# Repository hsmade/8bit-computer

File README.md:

# My 8-bit computer

This repo describes my homebrew 8-bit computer. 
It is loosely based on the works of  [Ben eater's 6502 computer](https://eater.net/6502), and others.

A build log can be found [here](https://hsmade.github.io/8bit-computer)

## Components
### CPU card
This card contains the CPU and the RAM.

To be built.

* more info [here](CPU/README.md)
* the schematics can be found [here](CPU/kicad/)

### ROM card
This card holds the rom, and exposes a pin header for programming.
I currently do the programming with an Arduino Mega (because I need a lot of IO ports).
The software for programming the eeprom can be found [here](ROM/programmer/README.md)

* more info [here](ROM/README.md).
* the schematic can be found [here](ROM/kicad/).

### Bus display card
This card shows the current contents of the address and data bus, and if the CPU is reading or writing.
I used the trick to alternate between 2 displays, using a timer, from Ben Eater.
This doesn't use the whole flip-flop setup though, as I use just 2 displays per 8 bits (hex).

* more info [here](bus-display/README.md)
* the schematic can be found [here](bus-display/kicad/).

### IO card
This card will interface with the outside world.
The idea is to control a 1602A display, and a serial port.

To be designed and built.

## Requirements
The following software is required to run makefiles:
* cc65
* platformio

## Memory map
http://wilsonminesco.com/6502primer/addr_decoding.html

| start | end  | what     | A15 | A14 | A13 | A12 | A11 | A10 | A9 | A8 | A3 | A2 |
|-------|------|----------|-----|-----|-----|-----|-----|-----|----|----|----|----|
| 0000  | 3FFF | RAM      |   0 |   0 |   x |   x |   x |   x |  x |  x |  x |  x |
| 4100  |      | ACIA 3-1 |   0 |   1 |   0 |   0 |   0 |   0 |  0 |  1 |  0 |  0 |
| 4104  |      | ACIA 3-2 |   0 |   1 |   0 |   0 |   0 |   0 |  0 |  1 |  0 |  1 |
| 4108  |      | ACIA 3-3 |   0 |   1 |   0 |   0 |   0 |   0 |  0 |  1 |  1 |  0 |
| 410C  |      | ACIA 3-4 |   0 |   1 |   0 |   0 |   0 |   0 |  0 |  1 |  1 |  1 |
| 4200  |      | ACIA 2-1 |   0 |   1 |   0 |   0 |   0 |   0 |  1 |  0 |  0 |  0 |
| 4204  |      | ACIA 2-2 |   0 |   1 |   0 |   0 |   0 |   0 |  1 |  0 |  0 |  1 |
| 4208  |      | ACIA 2-3 |   0 |   1 |   0 |   0 |   0 |   0 |  1 |  0 |  1 |  0 |
| 420C  |      | ACIA 2-4 |   0 |   1 |   0 |   0 |   0 |   0 |  1 |  0 |  1 |  1 |
| 4400  | 4403 | ACIA 1   |   0 |   1 |   0 |   0 |   0 |   1 |  0 |  0 |  0 |  0 |
| 4800  | 480F | VIA 3    |   0 |   1 |   0 |   0 |   1 |   0 |  0 |  0 |  x |  x |
| 5000  | 500F | VIA 2    |   0 |   1 |   0 |   1 |   0 |   0 |  0 |  0 |  x |  x |
| 6000  | 600F | VIA 1    |   0 |   1 |   1 |   0 |   0 |   0 |  0 |  0 |  x |  x |
| 8000  | FFFF | ROM      |   1 |   x |   x |   x |   x |   x |  x |  x |  x |  x |

`A1` and `A0` select registers inside each ACIA. `A3` through `A0`
select registers inside each VIA. `A7` through `A4` are not decoded in
this memory map.

## Bus

| Use | Port | Port | Use   |
|-----|------|------|-------|
| VSS | 1    | 40   | VSS   |
| X   | 2    | 39   | Phi 0 |
| X   | 3    | 38   | X     |
| +5V | 4    | 37   | +5V   |
| A0  | 5    | 36   | X     |
| A1  | 6    | 35   | CSb   |
| A2  | 7    | 34   | RES   |
| A3  | 8    | 33   | NMI   |
| A4  | 9    | 32   | IRQ   |
| A5  | 10   | 31   | Phi 1 |
| A6  | 11   | 30   | Phi 2 |
| A7  | 12   | 29   | RWb   |
| A8  | 13   | 28   | D7    |
| A9  | 14   | 27   | D6    |
| A10 | 15   | 26   | D5    |
| A11 | 16   | 25   | D4    |
| A12 | 17   | 24   | D3    |
| A13 | 18   | 23   | D2    |
| A14 | 19   | 22   | D1    |
| A15 | 20   | 21   | D0    |

## Datasheets
* NAND [74HC00](https://www.mouser.com/catalog/specsheets/nxp_74hc_hct00.pdf)
* CPU [W65C02](https://nl.mouser.com/datasheet/2/436/w65c02s-2572.pdf)
* Power transistor PNP [BD952](https://nl.mouser.com/datasheet/2/54/bd646-1159083.pdf)
* RAM [39SF010A7CPHE](https://nl.mouser.com/datasheet/2/268/20005022C-1832260.pdf)
* 7 segment display [INND-TS40Y*CB](https://nl.mouser.com/datasheet/2/180/INND-TS40_Series_V1.0-1485199.pdf)
* ROM [SST39SF010A](https://nl.mouser.com/datasheet/2/268/20005022C-1832260.pdf)
* ACIA [W65C51](https://nl.mouser.com/datasheet/2/436/WDC_Datasheet%20Update_20141024-1211725.pdf)
* PIO [W65C22](https://nl.mouser.com/datasheet/2/436/w65c22-1197.pdf)

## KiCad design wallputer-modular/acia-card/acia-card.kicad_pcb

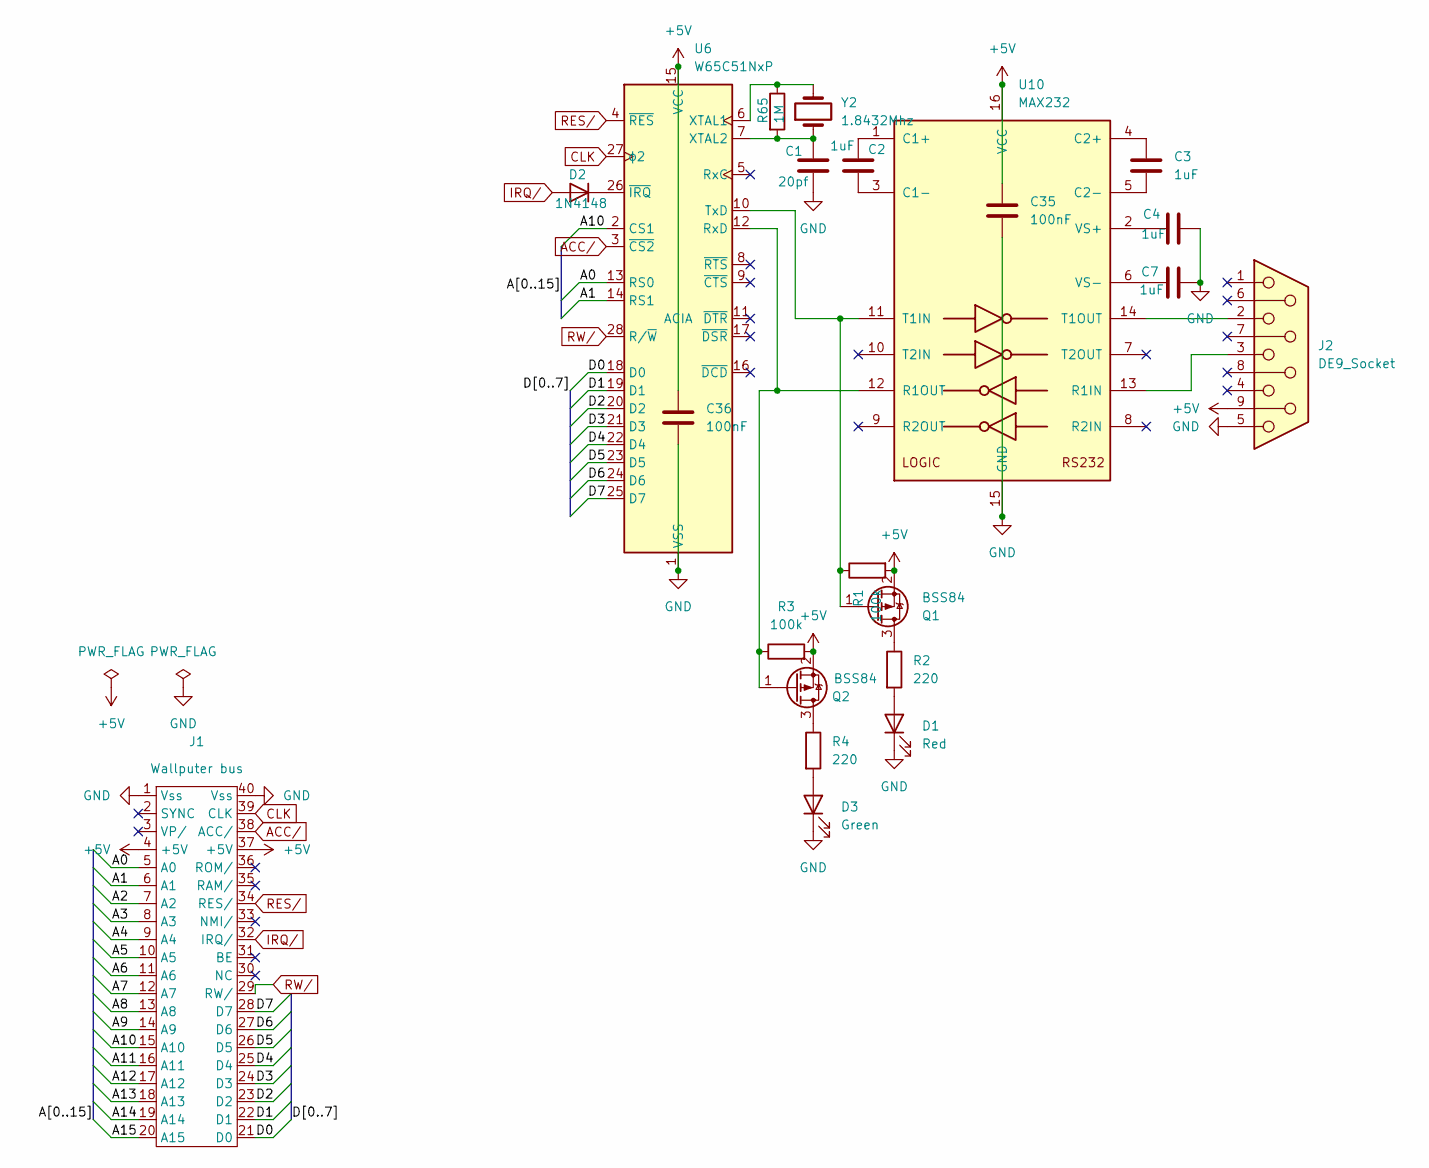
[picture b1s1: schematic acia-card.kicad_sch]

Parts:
C1: 20pf; C_Disc_D5.0mm_W2.5mm_P5.00mm
C2, C3, C4, C7: 1uF; C_Disc_D5.0mm_W2.5mm_P5.00mm
C35, C36: 100nF; C_Disc_D5.0mm_W2.5mm_P5.00mm
D1: Red; LED_D1.8mm_W3.3mm_H2.4mm
D2: 1N4148; D_DO-35_SOD27_P7.62mm_Horizontal
D3: Green; LED_D1.8mm_W3.3mm_H2.4mm
J1: Wallputer_Bus_Header
J2: DE9_Socket; DSUB-9_Pins_Horizontal_P2.77x2.84mm_EdgePinOffset4.94mm_Hou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
Q1, Q2: BSS84; SOT-23
R1, R3: 100k; R_Axial_DIN0204_L3.6mm_D1.6mm_P2.54mm_Vertical
R2, R4: 220; R_Axial_DIN0204_L3.6mm_D1.6mm_P2.54mm_Vertical
R65: 1M; R_Axial_DIN0204_L3.6mm_D1.6mm_P2.54mm_Vertical
U6: W65C51NxP; DIP-28_W15.24mm
U10: MAX232; DIP-16_W7.62mm_Socket
Y2: 1.8432Mhz; Crystal_HC18-U_Vertical

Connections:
+5V: C35.1, C36.1, J1.4 (+5V), J1.37 (+5V), J2.9, Q1.2 (S), Q2.2 (S), R1.2, R3.2, U6.15 (VCC), U10.16 (VCC)
/A0: J1.5 (A0), U6.13 (RS0)
/A1: J1.6 (A1), U6.14 (RS1)
/A2: J1.7 (A2)
/A3: J1.8 (A3)
/A4: J1.9 (A4)
/A5: J1.10 (A5)
/A6: J1.11 (A6)
/A7: J1.12 (A7)
/A8: J1.13 (A8)
/A9: J1.14 (A9)
/A10: J1.15 (A10), U6.2 (CS1)
/A11: J1.16 (A11)
/A12: J1.17 (A12)
/A13: J1.18 (A13)
/A14: J1.19 (A14)
/A15: J1.20 (A15)
/D0: J1.21 (D0), U6.18 (D0)
/D1: J1.22 (D1), U6.19 (D1)
/D2: J1.23 (D2), U6.20 (D2)
/D3: J1.24 (D3), U6.21 (D3)
/D4: J1.25 (D4), U6.22 (D4)
/D5: J1.26 (D5), U6.23 (D5)
/D6: J1.27 (D6), U6.24 (D6)
/D7: J1.28 (D7), U6.25 (D7)
ACC/: J1.38 (ACC/), U6.3 (~CS2)
CLK: J1.39 (CLK), U6.27 (ϕ2)
GND: C1.2, C4.2, C7.2, C35.2, C36.2, D1.1 (K), D3.1 (K), J1.1 (Vss), J1.40 (Vss), J2.5, U6.1 (VSS), U10.15 (GND)
IRQ/: D2.2 (A), J1.32 (IRQ/)
unnamed: D1.2 (A), R2.2
unnamed: D2.1 (K), U6.26 (~IRQ)
unnamed: D3.2 (A), R4.2
unnamed: Q1.3 (D), R2.1
unnamed: Q1.1 (G), R1.1, U6.10 (TxD), U10.11 (T1IN)
unnamed: Q2.3 (D), R4.1
unnamed: Q2.1 (G), R3.1, U6.12 (RxD), U10.12 (R1OUT)
unnamed: R65.1, U6.6 (XTAL1), Y2.2
unnamed: C1.1, R65.2, U6.7 (XTAL2), Y2.1
unnamed: C2.1, U10.1 (C1+)
unnamed: C2.2, U10.3 (C1-)
unnamed: C3.1, U10.4 (C2+)
unnamed: C3.2, U10.5 (C2-)
unnamed: J2.3, U10.13 (R1IN)
unnamed: J2.2, U10.14 (T1OUT)
unnamed: C4.1, U10.2 (VS+)
unnamed: C7.1, U10.6 (VS-)
RES/: J1.34 (RES/), U6.4 (~RES)
RW/: J1.29 (RW/), U6.28 (R/~W)

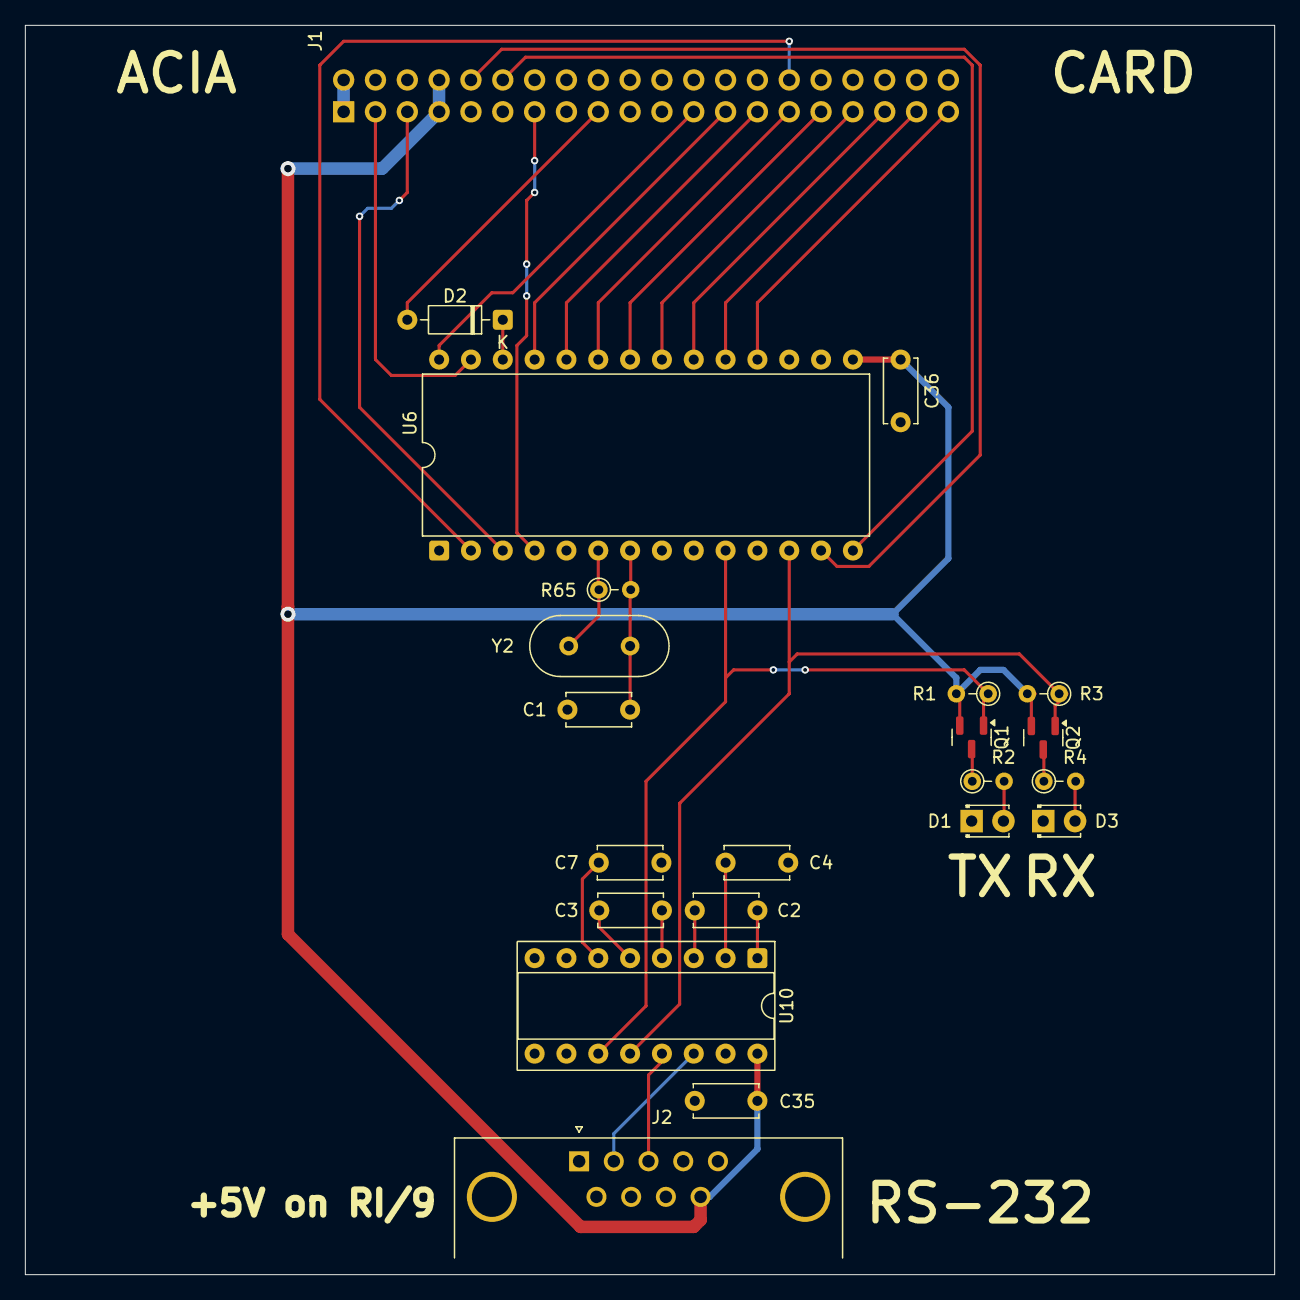
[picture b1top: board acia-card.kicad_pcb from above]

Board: 2 copper layers, 99.7 x 99.7 mm, 22 parts (0 on the bottom side), 35 nets.

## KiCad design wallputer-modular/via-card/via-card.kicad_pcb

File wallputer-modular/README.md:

# Modular Wall-Computer

## Setup
|  |  |  |  |
| -- | -- | -- | -- |
|  | [Clock Card](#clock-card) | [CPU Card](#cpu-card) | [Memory Card](#memory-card) |
| [Power Card](#power-card) | [Backplane Card](#backplane-card) | [Backplane Card](#backplane-card) | [Backplane Card](#backplane-card) |
|  | [Bus Display Card](#bus-display-card) | [ACIA Card](#acia-card) | [VIA Card](#via-card) |

## TODO

* finish up BOM using order
* check all footprints
* verify 555 circuits
* verify dual led circuit
* design rp2040 circuit
* verify clock switch circuit
* brightness via bars
* brightness RS-232 leds

## ACIA Card
Used for serial ports.

## Backplane Card

## Bus Display Card

## Clock Card
Generates the clock signal to steer the CPU and other components.

## CPU Card

## Memory Card

## Power Card
Power input and bus signal LEDs.

## VIA Card
I/O ports (LCD display, other stuff..)

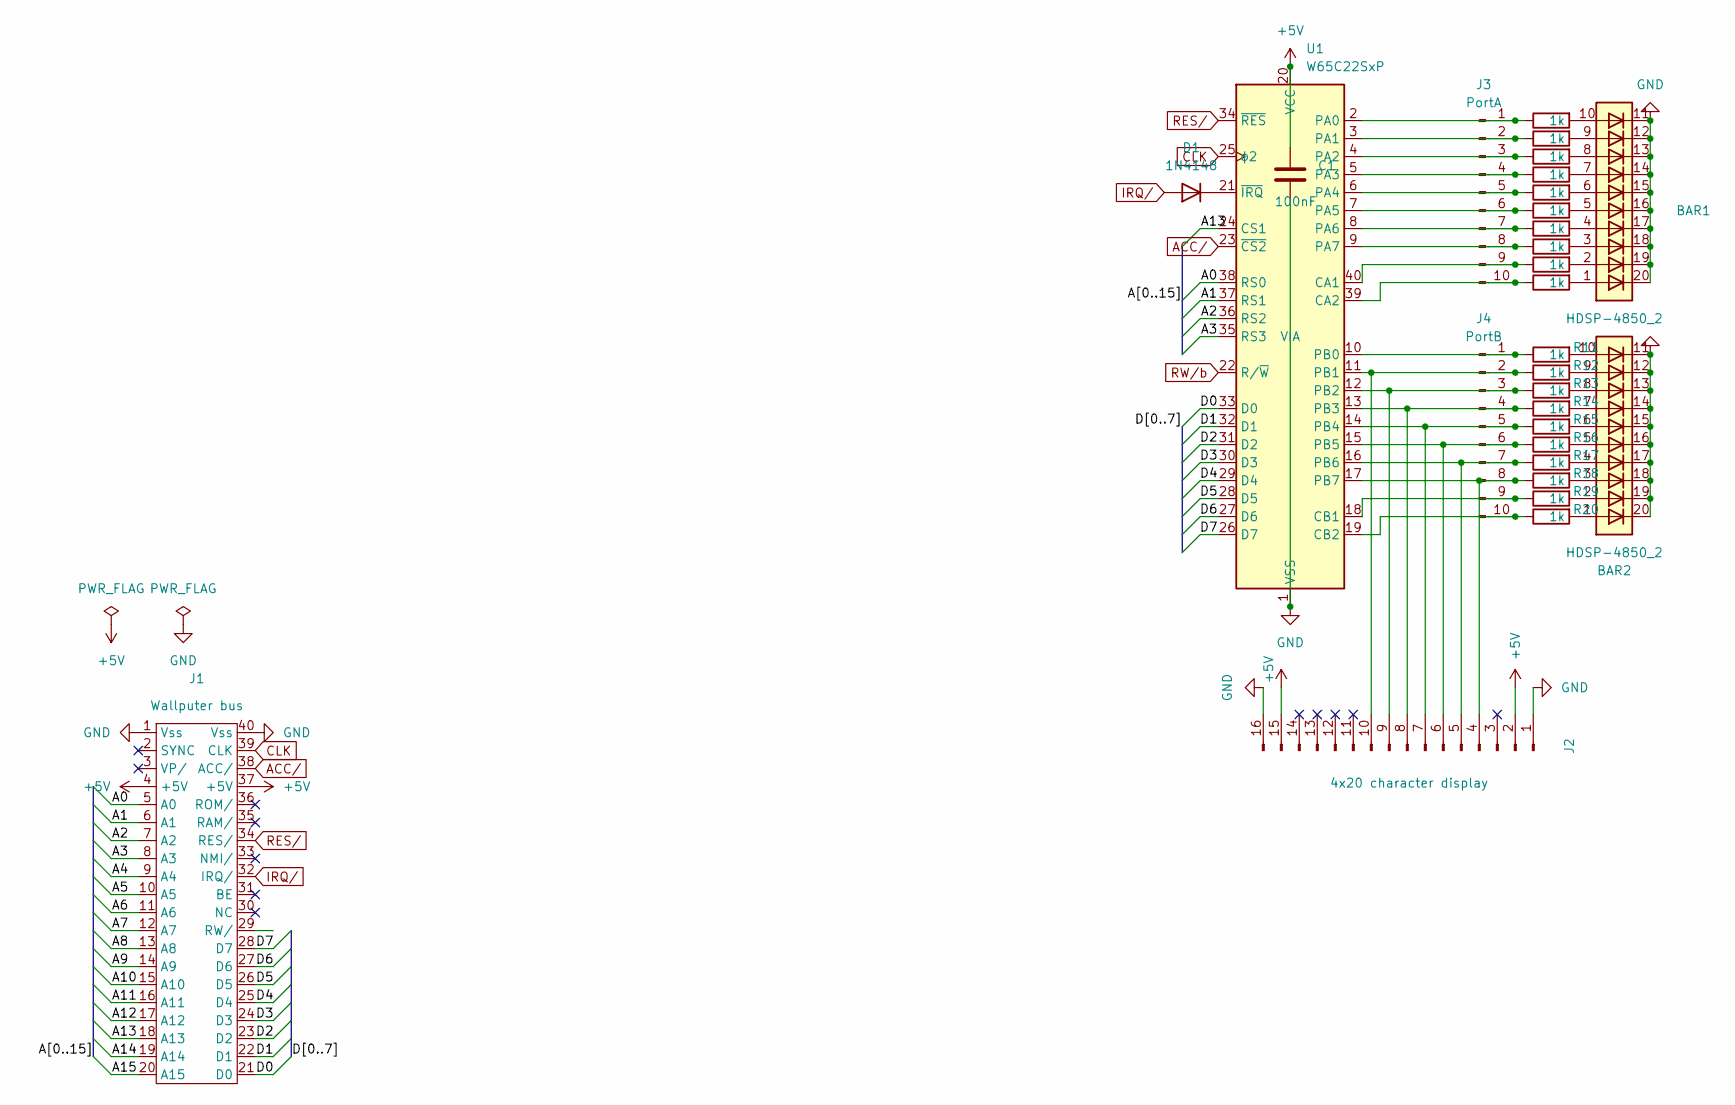
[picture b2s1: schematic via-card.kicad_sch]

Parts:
BAR1, BAR2: HDSP-4850_2; HDSP-4850
C1: 100nF; C_Disc_D5.0mm_W2.5mm_P5.00mm
D1: 1N4148; D_DO-35_SOD27_P7.62mm_Horizontal
J1: Wallputer_Bus_Header
J2: 4x20 character display; PinHeader_1x16_P2.54mm_Vertical
J3: PortA; PinHeader_1x10_P2.54mm_Vertical
J4: PortB; PinHeader_1x10_P2.54mm_Vertical
R1, R2, R3, R4, R5, R6, R7, R8, R9, R10, R11, R12, R13, R14, R15, R16, R17, R18, R19, R20: 1k; R_Axial_DIN0204_L3.6mm_D1.6mm_P2.54mm_Vertical
U1: W65C22SxP; DIP-40_W15.24mm

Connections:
+5V: C1.1, J1.4 (+5V), J1.37 (+5V), J2.2, J2.15, U1.20 (VCC)
/A0: J1.5 (A0), U1.38 (RS0)
/A1: J1.6 (A1), U1.37 (RS1)
/A2: J1.7 (A2), U1.36 (RS2)
/A3: J1.8 (A3), U1.35 (RS3)
/A4: J1.9 (A4)
/A5: J1.10 (A5)
/A6: J1.11 (A6)
/A7: J1.12 (A7)
/A8: J1.13 (A8)
/A9: J1.14 (A9)
/A10: J1.15 (A10)
/A11: J1.16 (A11)
/A12: J1.17 (A12)
/A13: J1.18 (A13), U1.24 (CS1)
/A14: J1.19 (A14)
/A15: J1.20 (A15)
/D0: J1.21 (D0), U1.33 (D0)
/D1: J1.22 (D1), U1.32 (D1)
/D2: J1.23 (D2), U1.31 (D2)
/D3: J1.24 (D3), U1.30 (D3)
/D4: J1.25 (D4), U1.29 (D4)
/D5: J1.26 (D5), U1.28 (D5)
/D6: J1.27 (D6), U1.27 (D6)
/D7: J1.28 (D7), U1.26 (D7)
ACC/: J1.38 (ACC/), U1.23 (~CS2)
CLK: J1.39 (CLK), U1.25 (ϕ2)
GND: BAR1.11 (K), BAR1.12 (K), BAR1.13 (K), BAR1.14 (K), BAR1.15 (K), BAR1.16 (K), BAR1.17 (K), BAR1.18 (K), BAR1.19 (K), BAR1.20 (K), BAR2.11 (K), BAR2.12 (K), BAR2.13 (K), BAR2.14 (K), BAR2.15 (K), BAR2.16 (K), BAR2.17 (K), BAR2.18 (K), BAR2.19 (K), BAR2.20 (K), C1.2, J1.1 (Vss), J1.40 (Vss), J2.1, J2.16, U1.1 (VSS)
IRQ/: D1.2 (A), J1.32 (IRQ/)
unnamed: BAR1.1 (A), R10.2
unnamed: BAR1.2 (A), R9.2
unnamed: BAR1.3 (A), R8.2
unnamed: BAR1.4 (A), R7.2
unnamed: BAR1.5 (A), R6.2
unnamed: BAR1.6 (A), R5.2
unnamed: BAR1.7 (A), R4.2
unnamed: BAR1.8 (A), R3.2
unnamed: BAR1.9 (A), R2.2
unnamed: BAR1.10 (A), R1.2
unnamed: BAR2.1 (A), R20.2
unnamed: BAR2.2 (A), R19.2
unnamed: BAR2.3 (A), R18.2
unnamed: BAR2.4 (A), R17.2
unnamed: BAR2.5 (A), R16.2
unnamed: BAR2.6 (A), R15.2
unnamed: BAR2.7 (A), R14.2
unnamed: BAR2.8 (A), R13.2
unnamed: BAR2.9 (A), R12.2
unnamed: BAR2.10 (A), R11.2
unnamed: D1.1 (K), U1.21 (~IRQ)
unnamed: J2.4, J4.8, R18.1, U1.17 (PB7)
unnamed: J2.5, J4.7, R17.1, U1.16 (PB6)
unnamed: J2.6, J4.6, R16.1, U1.15 (PB5)
unnamed: J2.7, J4.5, R15.1, U1.14 (PB4)
unnamed: J2.8, J4.4, R14.1, U1.13 (PB3)
unnamed: J2.9, J4.3, R13.1, U1.12 (PB2)
unnamed: J2.10, J4.2, R12.1, U1.11 (PB1)
unnamed: J3.1, R1.1, U1.2 (PA0)
unnamed: J3.2, R2.1, U1.3 (PA1)
unnamed: J3.3, R3.1, U1.4 (PA2)
unnamed: J3.4, R4.1, U1.5 (PA3)
unnamed: J3.5, R5.1, U1.6 (PA4)
unnamed: J3.6, R6.1, U1.7 (PA5)
unnamed: J3.7, R7.1, U1.8 (PA6)
unnamed: J3.8, R8.1, U1.9 (PA7)
unnamed: J3.9, R9.1, U1.40 (CA1)
unnamed: J3.10, R10.1, U1.39 (CA2)
unnamed: J4.1, R11.1, U1.10 (PB0)
unnamed: J4.9, R19.1, U1.18 (CB1)
unnamed: J4.10, R20.1, U1.19 (CB2)
RES/: J1.34 (RES/), U1.34 (~RES)
RW/b: U1.22 (R/~W)

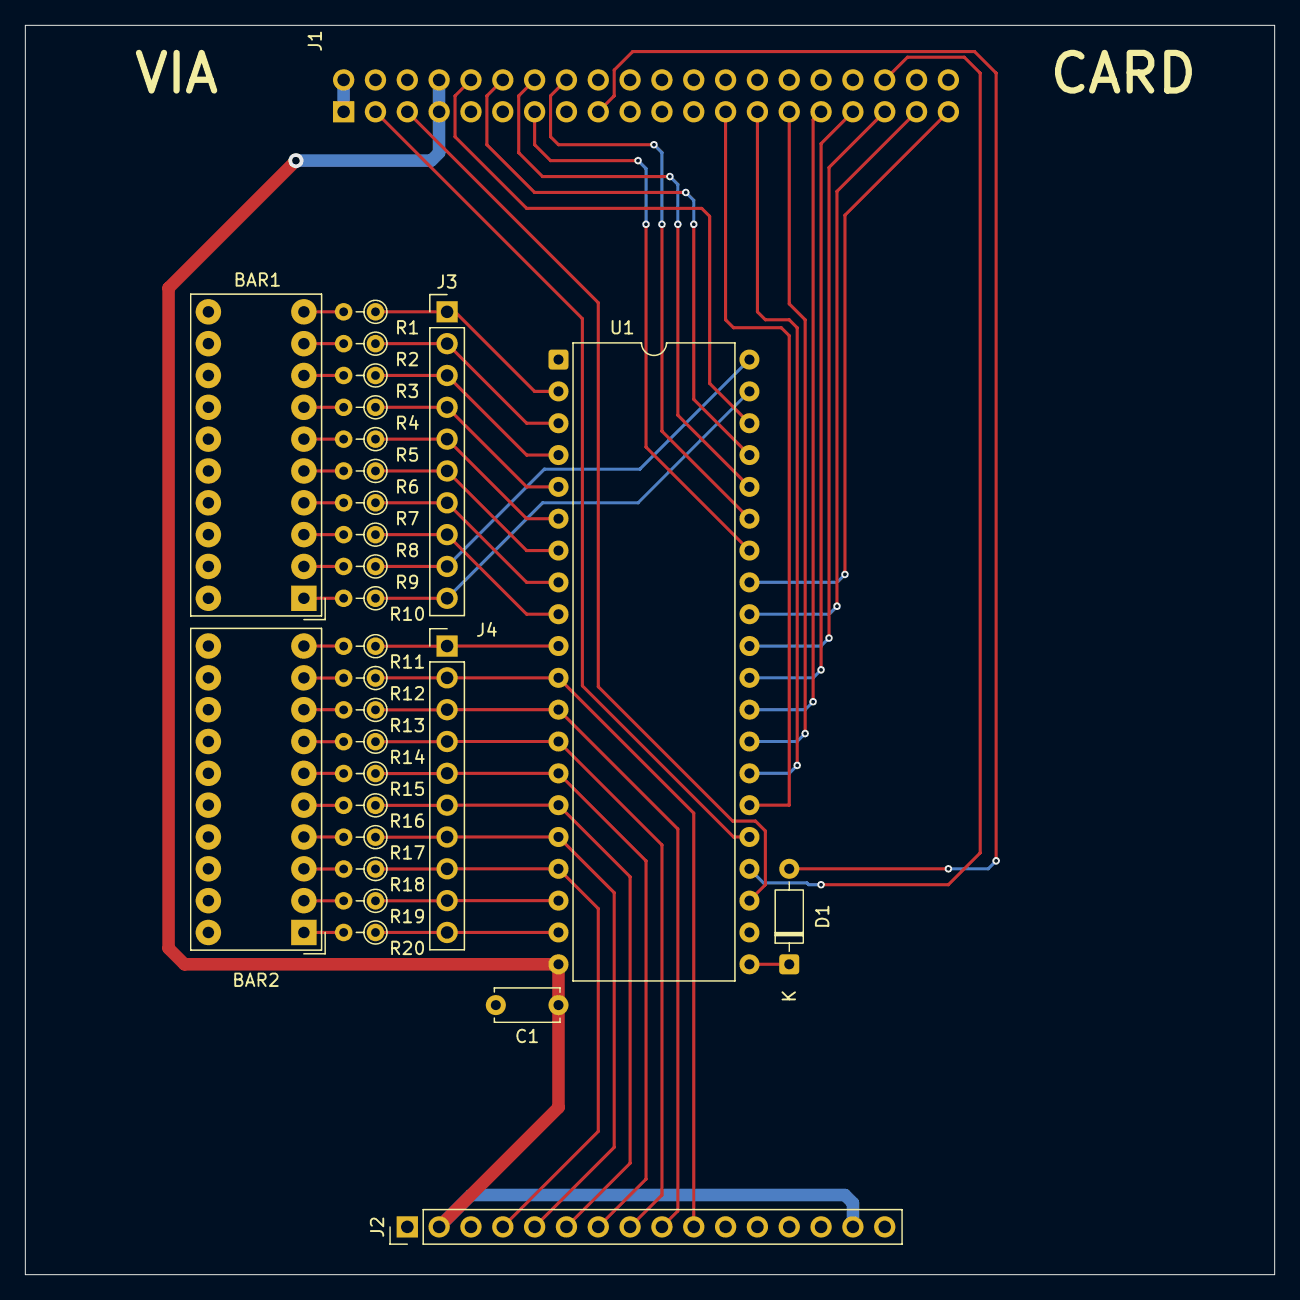
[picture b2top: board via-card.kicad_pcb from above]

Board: 2 copper layers, 99.7 x 99.7 mm, 29 parts (0 on the bottom side), 60 nets.

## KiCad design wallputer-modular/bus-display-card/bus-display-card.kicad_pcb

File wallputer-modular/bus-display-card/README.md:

# Bus Display Card

This card displays the contents of the address and the data bus in hexadecimals using the 7-segment displays.
The way this works is that each 'address' in the EEPROM has a value that corresponds to the right segments 
on the display. So for example, address 8 has value FE, so it lits up all segments.
The A8 signal is fed a square wave, so half the time we're using 0000-00FF and the 'right' display corresponding
to the right most byte, and the other half we're using FF00-FFFF and the 'left' display.
This way, we can re-use 1 EEPROM for 2 bytes data.

See [display-table.md](display-table.md) for a mapping. Use the script/makefie to generate the EEPROM binary.

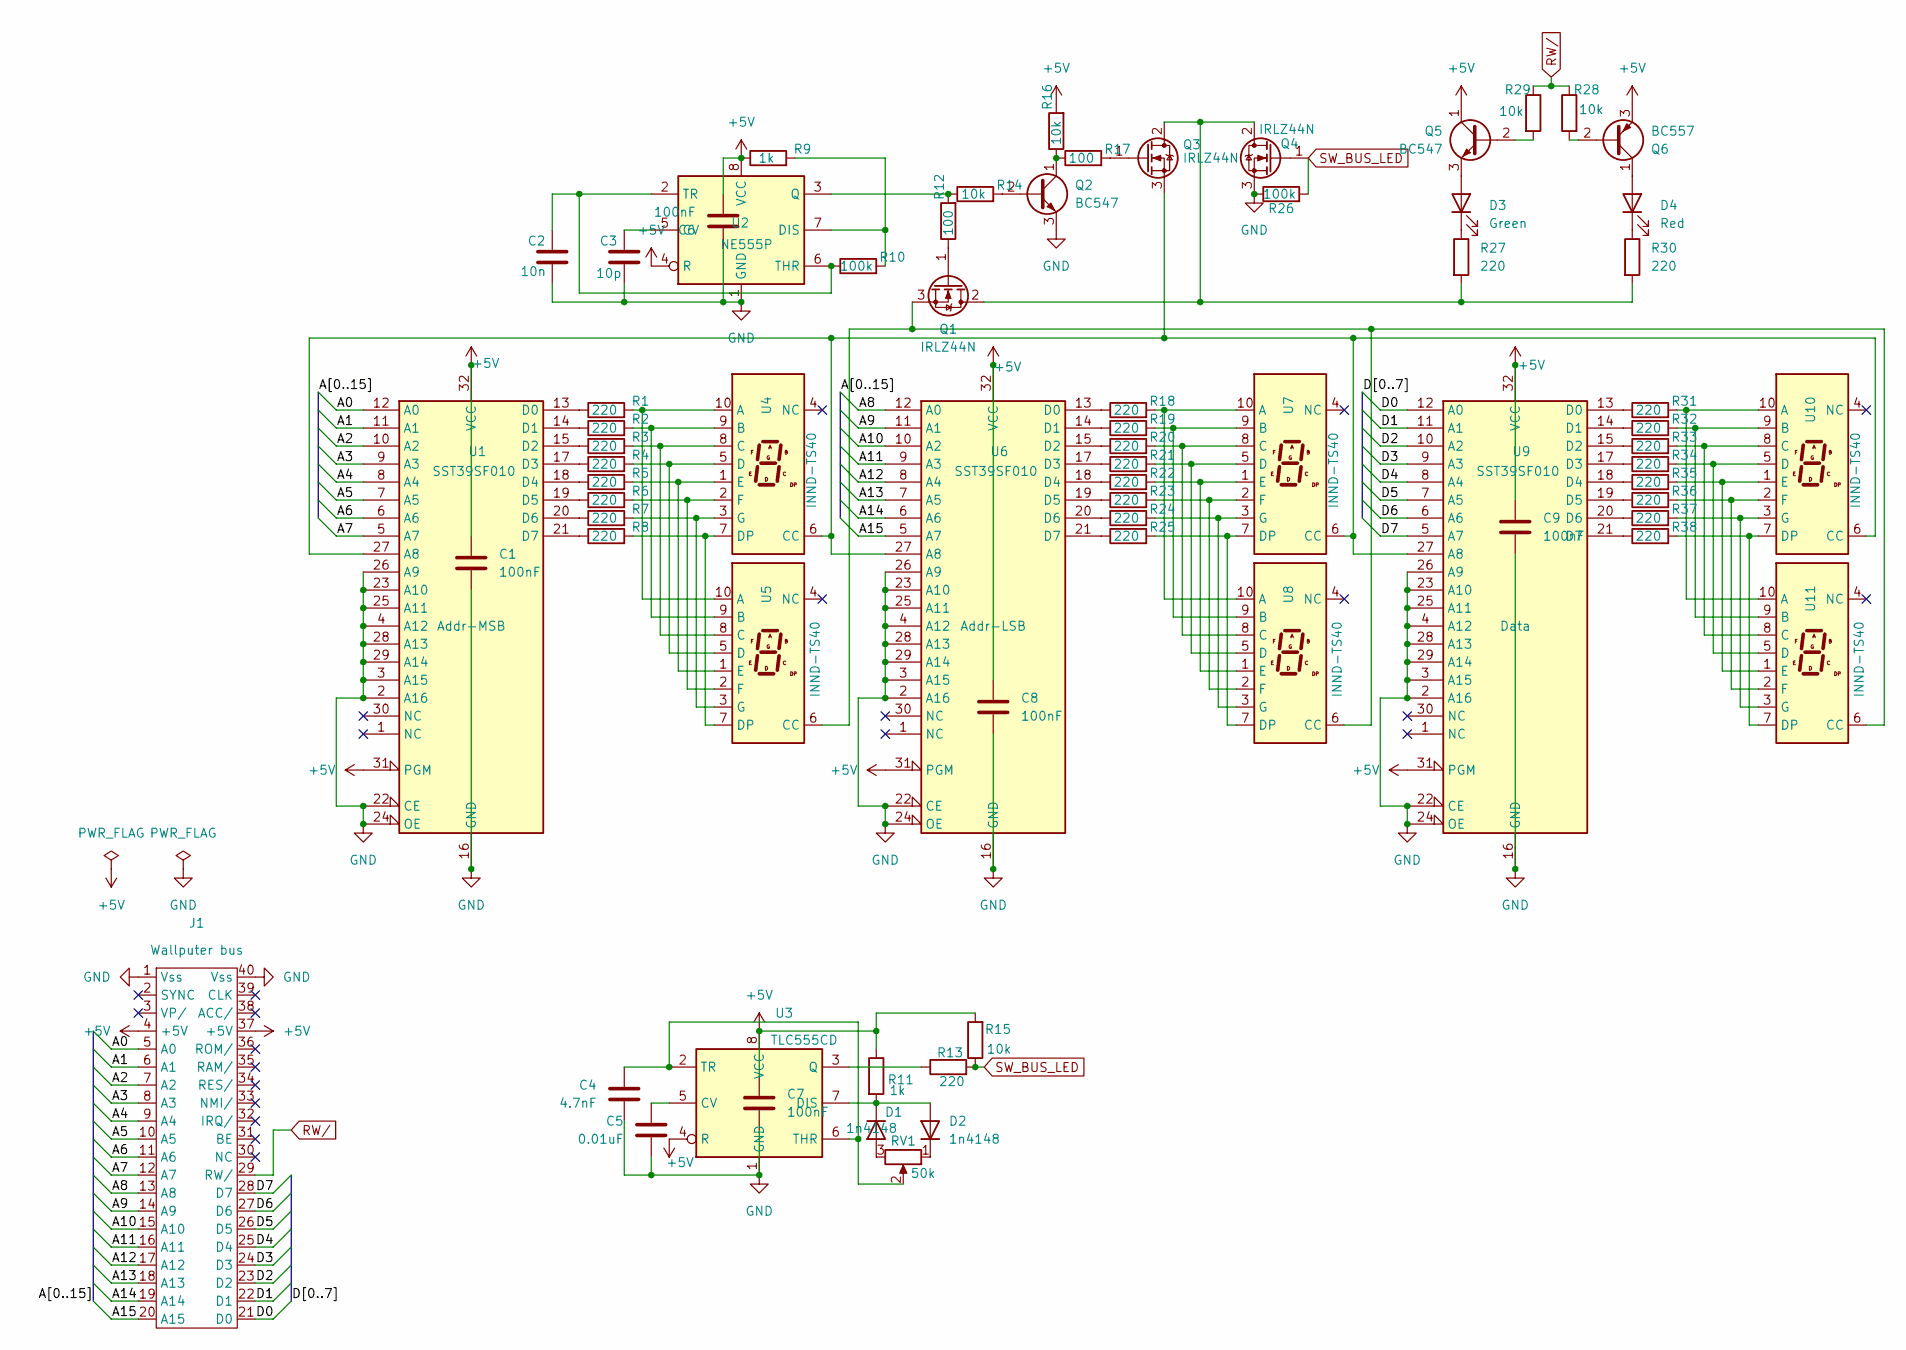
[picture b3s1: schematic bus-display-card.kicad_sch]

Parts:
C1, C6, C7, C8, C9: 100nF; C_Disc_D5.0mm_W2.5mm_P5.00mm
C2: 10n; C_Disc_D5.0mm_W2.5mm_P5.00mm
C3: 10p; C_Disc_D5.0mm_W2.5mm_P5.00mm
C4: 4.7nF; C_Disc_D5.0mm_W2.5mm_P5.00mm
C5: 0.01uF; C_Disc_D5.0mm_W2.5mm_P5.00mm
D1, D2: 1n4148; D_DO-35_SOD27_P7.62mm_Horizontal
D3: Green; LED_D3.0mm
D4: Red; LED_D3.0mm
J1: Wallputer_Bus_Header
Q1, Q3, Q4: IRLZ44N; TO-220-3_Vertical
Q2, Q5: BC547; TO-92_Inline
Q6: BC557; TO-92_Inline
R1, R2, R3, R4, R5, R6, R7, R8, R13, R18, R19, R20, R21, R22, R23, R24, R25, R27, R30, R31, R32, R33, R34, R35, R36, R37, R38: 220; R_Axial_DIN0204_L3.6mm_D1.6mm_P2.54mm_Vertical
R9, R11: 1k; R_Axial_DIN0204_L3.6mm_D1.6mm_P2.54mm_Vertical
R10, R26: 100k; R_Axial_DIN0204_L3.6mm_D1.6mm_P2.54mm_Vertical
R12, R17: 100; R_Axial_DIN0204_L3.6mm_D1.6mm_P2.54mm_Vertical
R14, R15, R16, R28, R29: 10k; R_Axial_DIN0204_L3.6mm_D1.6mm_P2.54mm_Vertical
RV1: 50k; Potentiometer_Alpha_RD901F-40-00D_Single_Vertical
U1, U6, U9: SST39SF010; DIP-32_W15.24mm_Socket
U2: NE555P; DIP-8_W7.62mm
U3: TLC555CD; DIP-8_W7.62mm
U4, U5, U7, U8, U10, U11: INND-TS40

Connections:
+5V: C1.1, C6.2, C7.1, C8.1, C9.1, J1.4 (+5V), J1.37 (+5V), Q5.1 (C), Q6.3 (E), R9.1, R11.1, R15.2, R16.2, U1.31 (PGM), U1.32 (VCC), U2.4 (R), U2.8 (VCC), U3.4 (R), U3.8 (VCC), U6.31 (PGM), U6.32 (VCC), U9.31 (PGM), U9.32 (VCC)
/A0: J1.5 (A0), U1.12 (A0)
/A1: J1.6 (A1), U1.11 (A1)
/A2: J1.7 (A2), U1.10 (A2)
/A3: J1.8 (A3), U1.9 (A3)
/A4: J1.9 (A4), U1.8 (A4)
/A5: J1.10 (A5), U1.7 (A5)
/A6: J1.11 (A6), U1.6 (A6)
/A7: J1.12 (A7), U1.5 (A7)
/A8: J1.13 (A8), U6.12 (A0)
/A9: J1.14 (A9), U6.11 (A1)
/A10: J1.15 (A10), U6.10 (A2)
/A11: J1.16 (A11), U6.9 (A3)
/A12: J1.17 (A12), U6.8 (A4)
/A13: J1.18 (A13), U6.7 (A5)
/A14: J1.19 (A14), U6.6 (A6)
/A15: J1.20 (A15), U6.5 (A7)
/D0: J1.21 (D0), U9.12 (A0)
/D1: J1.22 (D1), U9.11 (A1)
/D2: J1.23 (D2), U9.10 (A2)
/D3: J1.24 (D3), U9.9 (A3)
/D4: J1.25 (D4), U9.8 (A4)
/D5: J1.26 (D5), U9.7 (A5)
/D6: J1.27 (D6), U9.6 (A6)
/D7: J1.28 (D7), U9.5 (A7)
GND: C1.2, C2.2, C3.2, C4.2, C5.1, C6.1, C7.2, C8.2, C9.2, J1.1 (Vss), J1.40 (Vss), Q2.3 (E), Q4.3 (S), R26.1, U1.2 (A16), U1.3 (A15), U1.4 (A12), U1.16 (GND), U1.22 (CE), U1.23 (A10), U1.24 (OE), U1.25 (A11), U1.26 (A9), U1.28 (A13), U1.29 (A14), U2.1 (GND), U3.1 (GND), U6.2 (A16), U6.3 (A15), U6.4 (A12), U6.16 (GND), U6.22 (CE), U6.23 (A10), U6.24 (OE), U6.25 (A11), U6.26 (A9), U6.28 (A13), U6.29 (A14), U9.2 (A16), U9.3 (A15), U9.4 (A12), U9.16 (GND), U9.22 (CE), U9.23 (A10), U9.24 (OE), U9.25 (A11), U9.26 (A9), U9.28 (A13), U9.29 (A14)
unnamed: D1.2 (A), RV1.3
unnamed: D1.1 (K), D2.2 (A), R11.2, U3.7 (DIS)
unnamed: D2.1 (K), RV1.1
unnamed: D3.2 (A), Q5.3 (E)
unnamed: D3.1 (K), R27.1
unnamed: D4.2 (A), Q6.1 (C)
unnamed: D4.1 (K), R30.1
unnamed: Q1.2 (D), Q3.2 (D), Q4.2 (D), R27.2, R30.2
unnamed: Q1.1 (G), R12.1
unnamed: Q1.3 (S), U5.6 (CC), U8.6 (CC), U11.6 (CC)
unnamed: Q2.2 (B), R14.2
unnamed: Q2.1 (C), R16.1, R17.1
unnamed: Q3.1 (G), R17.2
unnamed: Q3.3 (S), U1.27 (A8), U4.6 (CC), U6.27 (A8), U7.6 (CC), U9.27 (A8), U10.6 (CC)
unnamed: Q5.2 (B), R28.2
unnamed: Q6.2 (B), R29.2
unnamed: R1.1, U1.13 (D0)
unnamed: R2.1, U1.14 (D1)
unnamed: R3.1, U1.15 (D2)
unnamed: R4.1, U1.17 (D3)
unnamed: R5.1, U1.18 (D4)
unnamed: R6.1, U1.19 (D5)
unnamed: R7.1, U1.20 (D6)
unnamed: R8.1, U1.21 (D7)
unnamed: C3.1, U2.5 (CV)
unnamed: R9.2, R10.2, U2.7 (DIS)
unnamed: R12.2, R14.1, U2.3 (Q)
unnamed: C2.1, R10.1, U2.2 (TR), U2.6 (THR)
unnamed: C5.2, U3.5 (CV)
unnamed: R13.1, U3.3 (Q)
unnamed: C4.1, RV1.2, U3.2 (TR), U3.6 (THR)
unnamed: R1.2, U4.10 (A), U5.10 (A)
unnamed: R2.2, U4.9 (B), U5.9 (B)
unnamed: R3.2, U4.8 (C), U5.8 (C)
unnamed: R4.2, U4.5 (D), U5.5 (D)
unnamed: R8.2, U4.7 (DP), U5.7 (DP)
unnamed: R5.2, U4.1 (E), U5.1 (E)
unnamed: R6.2, U4.2 (F), U5.2 (F)
unnamed: R7.2, U4.3 (G), U5.3 (G)
unnamed: R18.1, U6.13 (D0)
unnamed: R19.1, U6.14 (D1)
unnamed: R20.1, U6.15 (D2)
unnamed: R21.1, U6.17 (D3)
unnamed: R22.1, U6.18 (D4)
unnamed: R23.1, U6.19 (D5)
unnamed: R24.1, U6.20 (D6)
unnamed: R25.1, U6.21 (D7)
unnamed: R18.2, U7.10 (A), U8.10 (A)
unnamed: R19.2, U7.9 (B), U8.9 (B)
unnamed: R20.2, U7.8 (C), U8.8 (C)
unnamed: R21.2, U7.5 (D), U8.5 (D)
unnamed: R25.2, U7.7 (DP), U8.7 (DP)
unnamed: R22.2, U7.1 (E), U8.1 (E)
unnamed: R23.2, U7.2 (F), U8.2 (F)
unnamed: R24.2, U7.3 (G), U8.3 (G)
unnamed: R31.1, U9.13 (D0)
unnamed: R32.1, U9.14 (D1)
unnamed: R33.1, U9.15 (D2)
unnamed: R34.1, U9.17 (D3)
unnamed: R35.1, U9.18 (D4)
unnamed: R36.1, U9.19 (D5)
unnamed: R37.1, U9.20 (D6)
unnamed: R38.1, U9.21 (D7)
unnamed: R31.2, U10.10 (A), U11.10 (A)
unnamed: R32.2, U10.9 (B), U11.9 (B)
unnamed: R33.2, U10.8 (C), U11.8 (C)
unnamed: R34.2, U10.5 (D), U11.5 (D)
unnamed: R38.2, U10.7 (DP), U11.7 (DP)
unnamed: R35.2, U10.1 (E), U11.1 (E)
unnamed: R36.2, U10.2 (F), U11.2 (F)
unnamed: R37.2, U10.3 (G), U11.3 (G)
RW/: J1.29 (RW/), R28.1, R29.1
SW_BUS_LED: Q4.1 (G), R13.2, R15.1, R26.2

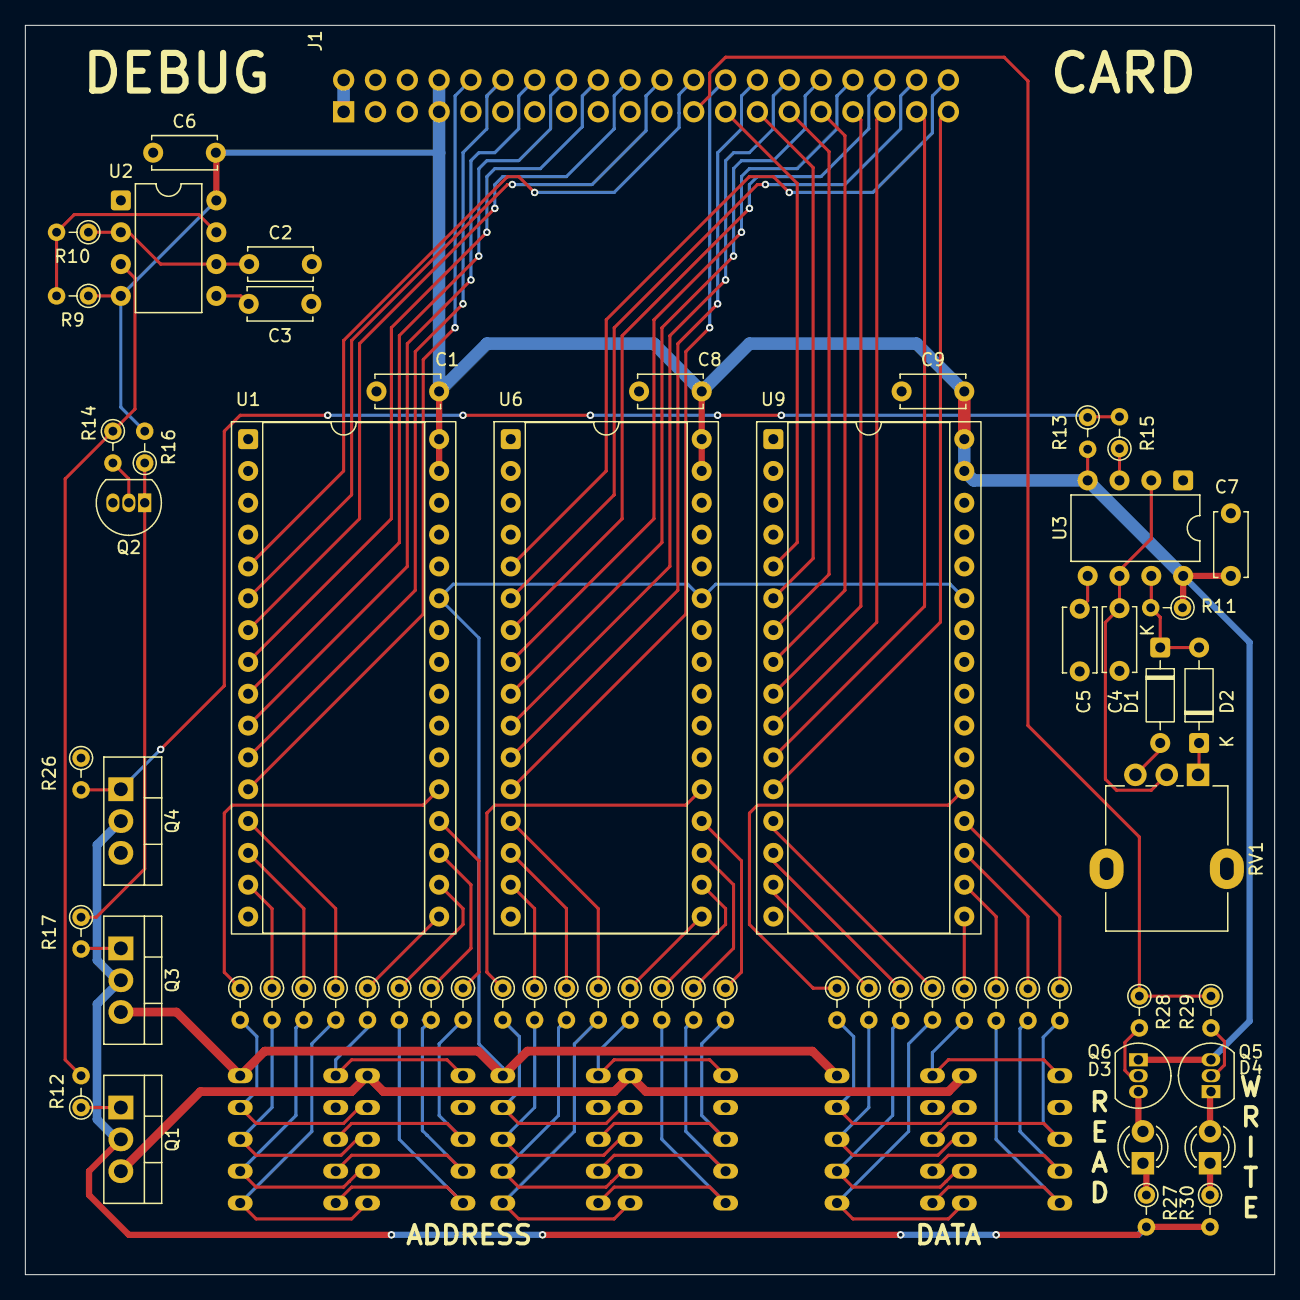
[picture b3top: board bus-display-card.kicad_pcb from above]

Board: 2 copper layers, 99.7 x 99.7 mm, 70 parts (0 on the bottom side), 99 nets.

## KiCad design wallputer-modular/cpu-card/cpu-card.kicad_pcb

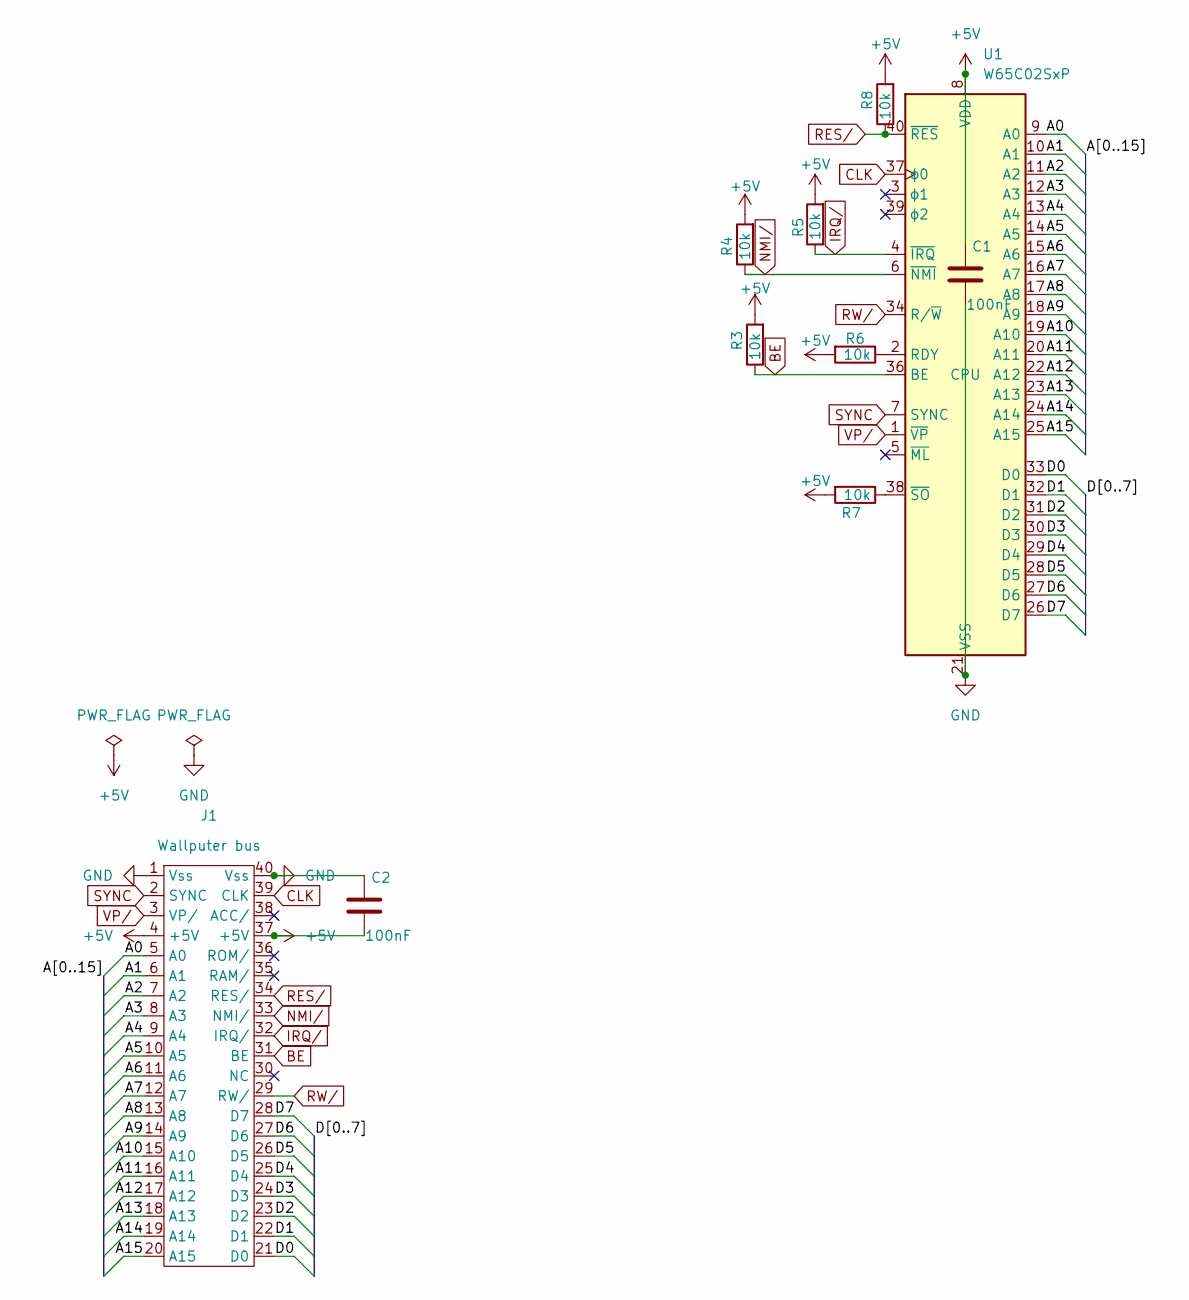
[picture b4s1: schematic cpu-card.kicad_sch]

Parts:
C1, C2: 100nF; C_Disc_D5.0mm_W2.5mm_P5.00mm
J1: Wallputer_Bus_Header
R3, R4, R5, R6, R7, R8: 10k; R_Axial_DIN0204_L3.6mm_D1.6mm_P2.54mm_Vertical
U1: W65C02SxP; DIP-40_W15.24mm_Socket

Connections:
+5V: C1.1, C2.2, J1.4 (+5V), J1.37 (+5V), R3.2, R4.2, R5.2, R6.2, R7.2, R8.2, U1.8 (VDD)
/A0: J1.5 (A0), U1.9 (A0)
/A1: J1.6 (A1), U1.10 (A1)
/A2: J1.7 (A2), U1.11 (A2)
/A3: J1.8 (A3), U1.12 (A3)
/A4: J1.9 (A4), U1.13 (A4)
/A5: J1.10 (A5), U1.14 (A5)
/A6: J1.11 (A6), U1.15 (A6)
/A7: J1.12 (A7), U1.16 (A7)
/A8: J1.13 (A8), U1.17 (A8)
/A9: J1.14 (A9), U1.18 (A9)
/A10: J1.15 (A10), U1.19 (A10)
/A11: J1.16 (A11), U1.20 (A11)
/A12: J1.17 (A12), U1.22 (A12)
/A13: J1.18 (A13), U1.23 (A13)
/A14: J1.19 (A14), U1.24 (A14)
/A15: J1.20 (A15), U1.25 (A15)
/D0: J1.21 (D0), U1.33 (D0)
/D1: J1.22 (D1), U1.32 (D1)
/D2: J1.23 (D2), U1.31 (D2)
/D3: J1.24 (D3), U1.30 (D3)
/D4: J1.25 (D4), U1.29 (D4)
/D5: J1.26 (D5), U1.28 (D5)
/D6: J1.27 (D6), U1.27 (D6)
/D7: J1.28 (D7), U1.26 (D7)
BE: J1.31 (BE), R3.1, U1.36 (BE)
CLK: J1.39 (CLK), U1.37 (ϕ0)
GND: C1.2, C2.1, J1.1 (Vss), J1.40 (Vss), U1.21 (VSS)
IRQ/: J1.32 (IRQ/), R5.1, U1.4 (~IRQ)
NMI/: J1.33 (NMI/), R4.1, U1.6 (~NMI)
unnamed: R6.1, U1.2 (RDY)
unnamed: R7.1, U1.38 (~SO)
RES/: J1.34 (RES/), R8.1, U1.40 (~RES)
RW/: J1.29 (RW/), U1.34 (R/~W)
SYNC: J1.2 (SYNC), U1.7 (SYNC)
VP/: J1.3 (VP/), U1.1 (~VP)
